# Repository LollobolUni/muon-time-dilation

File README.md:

# Cosmic muons and the stretching of time

A self-built experiment to measure the lifetime of cosmic-ray muons and to show, with data taken from cable cars in the Alps, that moving clocks run slow.

> [!TIP]
> New to the project? The [project overview (PDF)](docs/muon-time-dilation_project-overview.pdf) is a good place to start: in ten illustrated pages it explains the physics, how the detector works and what comes next.

Muons are created about 15 km above the ground and live on average 2.2 µs. Without special relativity almost none of them would reach the surface. The experiment has two parts:

1. **Muon lifetime at rest.** A one-litre plastic scintillator stops about a thousand muons a day. The time between the flash of the stopping muon and the flash of its decay electron gives the lifetime, with a target precision of 2–3%.
2. **Muon flux versus altitude.** Two small scintillator tiles in coincidence, with lead in between, count muons at 5–6 stops from Milan up to about 3000 m. Without time dilation the flux at 3000 m would be about 95 times that on the plain; with relativity, less than twice.

## Status

Design stage (November 2026). The electronics, firmware and mechanics are designed; the timer firmware has been tested on real hardware. Assembly and the first measurements are next.

## Repository structure

| Folder | Contents |
|---|---|
| `docs/` | Project overview (PDF) |
| `hardware/kicad/` | KiCad projects of the two circuit boards, with the project library |
| `hardware/schematics/` | Schematics and board layouts as PDF |
| `hardware/gerbers/` | Manufacturing files for the two boards |
| `hardware/bom/` | Bills of materials, one per board |
| `mechanics/parts/` | Parts to 3D-print, as STEP files |
| `mechanics/assemblies/` | Complete assemblies of the block detector and of the tile module |
| `mechanics/drawings/` | Drawings of the threaded inserts for the two enclosures |
| `firmware/timer/` | Four-channel timer for the Raspberry Pi Pico 2 |
| `firmware/pulse-generator/` | Test pulse generator for the timer (Raspberry Pi Pico 2) |
| `firmware/tools/` | Script to record a timer test from the PC |

## Hardware

| Board | Size | Function |
|---|---|---|
| PCB-401, channel board | 40 × 40 mm | One SiPM (onsemi MicroFC-60035) with bias filter, pulse shaping, amplifier (OPA356) and fast comparator (TLV3501). One board per SiPM; the same board fits the block and the tiles. |
| PCB-402, base board | 100 × 64 mm | Raspberry Pi Pico 2 W timer, SiPM bias supply (MAX5026, 22.1–28.2 V), analogue 3.3 V, four threshold outputs, four channel connectors, pressure sensor and microSD headers. |

- The KiCad projects are saved with KiCad 10. `PCB-402` uses the project library stored in the `PCB-401` folder, so keep the two folders side by side.
- Channel cables are straight six-way JST PH cables, pin 1 to pin 1: 1 HV, 2 GND, 3 THR, 4 +3.3 V analogue, 5 GND, 6 OUT.
- The SiPM centre paddle (pin 5) is left unsoldered.
- The bill of materials lists manufacturer and LCSC part numbers. Where the original part was not available, the substitute is noted in the `Note` column.

## Mechanics

The enclosures are designed for SLA printing in resin. Parts `3DP-301` (block enclosure) and `3DP-311` (tile enclosure, two copies) take four M3 × 6.25 mm threaded inserts each, as shown in the drawings. All parts are oriented with Z up and the opening towards +Z.

| Part | Quantity |
|---|---|
| `3DP-301` Block enclosure | 1 |
| `3DP-302` Block lid | 1 |
| `3DP-303` SiPM holder, block | 2 |
| `3DP-304` Spring caps (four joined) | 1 |
| `3DP-311` Tile enclosure | 2 |
| `3DP-312` Tile lid | 2 |
| `3DP-313` SiPM holder, tile | 2 |

## Firmware

The timer runs on a Raspberry Pi Pico 2 (the base board also accepts the Pico 2 W, which has the same pinout). It timestamps rising edges on GP2–GP5 with a step of two system-clock cycles (13.3 ns at 150 MHz), using one PIO state machine per channel and DMA. Events are sent over USB serial as `channel,time_in_steps`; lines starting with `#` are header and status lines.

Ready-to-flash `.uf2` files are included: hold BOOTSEL, connect the Pico and copy the file onto the drive that appears. To build from source with the Raspberry Pi Pico SDK (2.x):

```
cd firmware/timer
mkdir build && cd build
cmake .. -DPICO_SDK_PATH=/path/to/pico-sdk
make
```

The pulse generator produces pairs of pulses at known distances or with exponentially distributed delays (mean 2.197 µs), to test the timer before the detector is built. `firmware/tools/record_timer_test.py` records a test from both boards (requires `pyserial`).

## Author

Lorenzo Bologna, Physics Engineering, Politecnico di Milano.

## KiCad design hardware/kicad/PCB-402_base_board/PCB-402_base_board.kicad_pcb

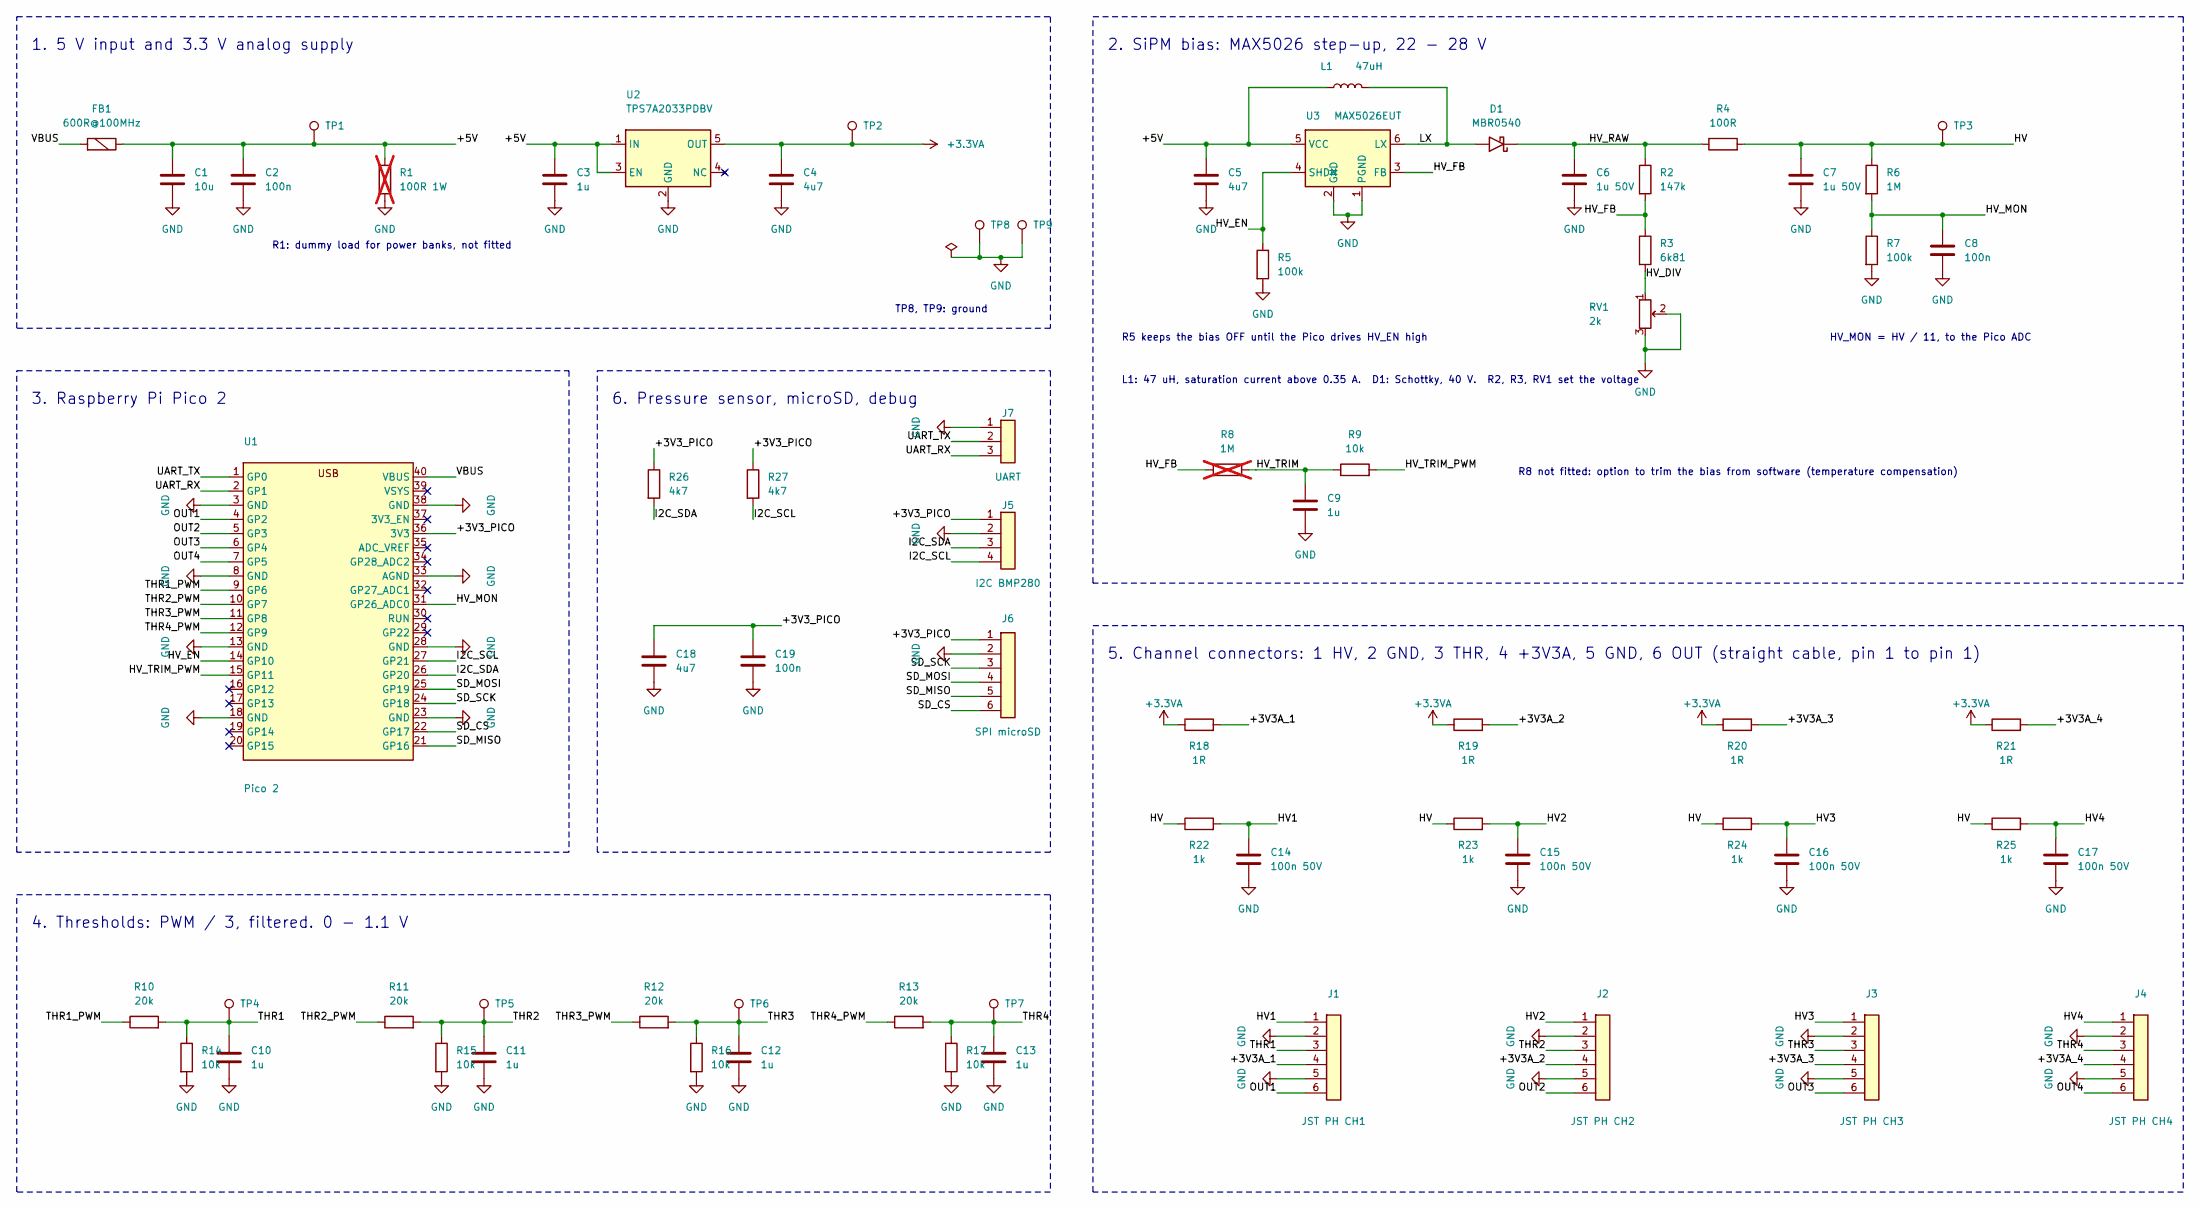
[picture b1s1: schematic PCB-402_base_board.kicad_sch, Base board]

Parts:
C1: 10u; C_0805_2012Metric_Pad1.18x1.45mm_HandSolder
C2, C8, C19: 100n; C_0805_2012Metric_Pad1.18x1.45mm_HandSolder
C3, C9, C10, C11, C12, C13: 1u; C_0805_2012Metric_Pad1.18x1.45mm_HandSolder
C4, C5, C18: 4u7; C_0805_2012Metric_Pad1.18x1.45mm_HandSolder
C6, C7: 1u 50V; C_0805_2012Metric_Pad1.18x1.45mm_HandSolder
C14, C15, C16, C17: 100n 50V; C_0805_2012Metric_Pad1.18x1.45mm_HandSolder
D1: MBR0540; D_SOD-123
FB1: 600R@100MHz; R_0805_2012Metric_Pad1.20x1.40mm_HandSolder
J1: JST PH CH1; JST_PH_B6B-PH-K_1x06_P2.00mm_Vertical
J2: JST PH CH2; JST_PH_B6B-PH-K_1x06_P2.00mm_Vertical
J3: JST PH CH3; JST_PH_B6B-PH-K_1x06_P2.00mm_Vertical
J4: JST PH CH4; JST_PH_B6B-PH-K_1x06_P2.00mm_Vertical
J5: I2C BMP280; PinHeader_1x04_P2.54mm_Vertical
J6: SPI microSD; PinHeader_1x06_P2.54mm_Vertical
J7: UART; PinHeader_1x03_P2.54mm_Vertical
L1: 47uH; L_Bourns_SRN6045TA
R1: 100R 1W; R_2512_6332Metric_Pad1.40x3.35mm_HandSolder; not fitted
R2: 147k; R_0805_2012Metric_Pad1.20x1.40mm_HandSolder
R3: 6k81; R_0805_2012Metric_Pad1.20x1.40mm_HandSolder
R4: 100R; R_0805_2012Metric_Pad1.20x1.40mm_HandSolder
R5, R7: 100k; R_0805_2012Metric_Pad1.20x1.40mm_HandSolder
R6: 1M; R_0805_2012Metric_Pad1.20x1.40mm_HandSolder
R8: 1M; R_0805_2012Metric_Pad1.20x1.40mm_HandSolder; not fitted
R9, R14, R15, R16, R17: 10k; R_0805_2012Metric_Pad1.20x1.40mm_HandSolder
R10, R11, R12, R13: 20k; R_0805_2012Metric_Pad1.20x1.40mm_HandSolder
R18, R19, R20, R21: 1R; R_0805_2012Metric_Pad1.20x1.40mm_HandSolder
R22, R23, R24, R25: 1k; R_1206_3216Metric_Pad1.30x1.75mm_HandSolder
R26, R27: 4k7; R_0805_2012Metric_Pad1.20x1.40mm_HandSolder
RV1: 2k; Potentiometer_Bourns_3296W_Vertical
TP1, TP2, TP3, TP4, TP5, TP6, TP7, TP8, TP9: TestPoint; TestPoint_Pad_D1.5mm
U1: Pico 2; RaspberryPi_Pico2_Sockets
U2: TPS7A2033PDBV; SOT-23-5
U3: MAX5026EUT; SOT-23-6

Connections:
+3.3VA: C4.1, R18.1, R19.1, R20.1, R21.1, TP2.1 (1_1), U2.5 (OUT)
/+3V3A_1: J1.4, R18.2
/+3V3A_2: J2.4, R19.2
/+3V3A_3: J3.4, R20.2
/+3V3A_4: J4.4, R21.2
/+3V3_PICO: C18.1, C19.1, J5.1, J6.1, R26.1, R27.1, U1.36 (3V3)
/+5V: C1.1, C2.1, C3.1, C5.1, FB1.2, L1.1, R1.1, TP1.1 (1_1), U2.1 (IN), U2.3 (EN), U3.5 (VCC)
/HV: C7.1, R4.2, R6.1, R22.1, R23.1, R24.1, R25.1, TP3.1 (1_1)
/HV1: C14.1, J1.1, R22.2
/HV2: C15.1, J2.1, R23.2
/HV3: C16.1, J3.1, R24.2
/HV4: C17.1, J4.1, R25.2
/HV_DIV: R3.2, RV1.1
/HV_EN: R5.1, U1.14 (GP10), U3.4 (SHDN)
/HV_FB: R2.2, R3.1, R8.1, U3.3 (FB)
/HV_MON: C8.1, R6.2, R7.1, U1.31 (GP26_ADC0)
/HV_RAW: C6.1, D1.1 (K), R2.1, R4.1
/HV_TRIM: C9.1, R8.2, R9.1
/HV_TRIM_PWM: R9.2, U1.15 (GP11)
/I2C_SCL: J5.4, R27.2, U1.27 (GP21)
/I2C_SDA: J5.3, R26.2, U1.26 (GP20)
/LX: D1.2 (A), L1.2, U3.6 (LX)
/OUT1: J1.6, U1.4 (GP2)
/OUT2: J2.6, U1.5 (GP3)
/OUT3: J3.6, U1.6 (GP4)
/OUT4: J4.6, U1.7 (GP5)
/SD_CS: J6.6, U1.22 (GP17)
/SD_MISO: J6.5, U1.21 (GP16)
/SD_MOSI: J6.4, U1.25 (GP19)
/SD_SCK: J6.3, U1.24 (GP18)
/THR1: C10.1, J1.3, R10.2, R14.1, TP4.1 (1_1)
/THR1_PWM: R10.1, U1.9 (GP6)
/THR2: C11.1, J2.3, R11.2, R15.1, TP5.1 (1_1)
/THR2_PWM: R11.1, U1.10 (GP7)
/THR3: C12.1, J3.3, R12.2, R16.1, TP6.1 (1_1)
/THR3_PWM: R12.1, U1.11 (GP8)
/THR4: C13.1, J4.3, R13.2, R17.1, TP7.1 (1_1)
/THR4_PWM: R13.1, U1.12 (GP9)
/UART_RX: J7.3, U1.2 (GP1)
/UART_TX: J7.2, U1.1 (GP0)
/VBUS: FB1.1, U1.40 (VBUS)
GND: C1.2, C2.2, C3.2, C4.2, C5.2, C6.2, C7.2, C8.2, C9.2, C10.2, C11.2, C12.2, C13.2, C14.2, C15.2, C16.2, C17.2, C18.2, C19.2, J1.2, J1.5, J2.2, J2.5, J3.2, J3.5, J4.2, J4.5, J5.2, J6.2, J7.1, R1.2, R5.2, R7.2, R14.2, R15.2, R16.2, R17.2, RV1.2, RV1.3, TP8.1 (1_1), TP9.1 (1_1), U1.3 (GND), U1.8 (GND), U1.13 (GND), U1.18 (GND), U1.23 (GND), U1.28 (GND), U1.33 (AGND), U1.38 (GND), U2.2 (GND), U3.1 (PGND), U3.2 (GND)

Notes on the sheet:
1. 5 V input and 3.3 V analog supply
R1: dummy load for power banks, not fitted
TP8, TP9: ground
2. SiPM bias: MAX5026 step-up, 22 - 28 V
R5 keeps the bias OFF until the Pico drives HV_EN high
L1: 47 uH, saturation current above 0.35 A. D1: Schottky, 40 V. R2, R3, RV1 set the voltage
HV_MON = HV / 11, to the Pico ADC
R8 not fitted: option to trim the bias from software (temperature compensation)
3. Raspberry Pi Pico 2
6. Pressure sensor, microSD, debug
4. Thresholds: PWM / 3, filtered. 0 - 1.1 V
5. Channel connectors: 1 HV, 2 GND, 3 THR, 4 +3V3A, 5 GND, 6 OUT (straight cable, pin 1 to pin 1)

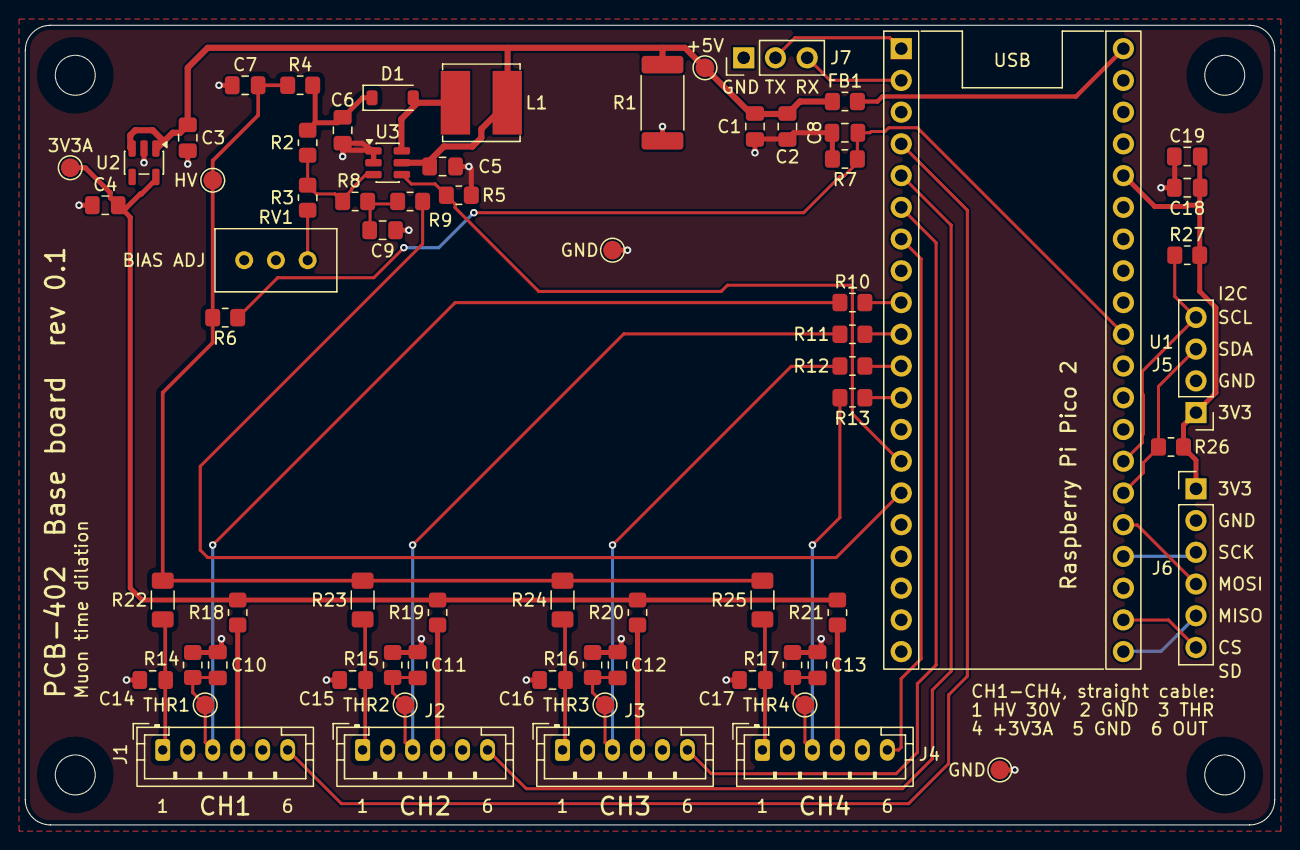
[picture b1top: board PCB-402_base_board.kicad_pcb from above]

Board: 2 copper layers, 100.0 x 64.0 mm, 73 parts (0 on the bottom side), 42 nets.

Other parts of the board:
H1, H2, H3, H4: M3; MountingHole_3.2mm_M3

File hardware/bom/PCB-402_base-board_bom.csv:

References,Qty,Value,Footprint,Manufacturer,MPN,LCSC,Note,Description
C1,1,10u,C_0805_2012Metric_Pad1.18x1.45mm_HandSolder,TDK,C2012X5R1E106KT000N,C329933,,Unpolarized capacitor
"C2, C8, C19",3,100n,C_0805_2012Metric_Pad1.18x1.45mm_HandSolder,Samsung,CL21B104KBCNNNC,C1711,,Unpolarized capacitor
"C3, C9, C10, C11, C12, C13",6,1u,C_0805_2012Metric_Pad1.18x1.45mm_HandSolder,YAGEO,CC0805KKX7R9BB105,C91185,,Unpolarized capacitor
"C4, C5, C18",3,4u7,C_0805_2012Metric_Pad1.18x1.45mm_HandSolder,Samsung,CL21A475KAQNNNE,C1779,,Unpolarized capacitor
"C6, C7",2,1u 50V,C_0805_2012Metric_Pad1.18x1.45mm_HandSolder,YAGEO,CC0805KKX7R9BB105,C91185,,Unpolarized capacitor
"C14, C15, C16, C17",4,100n 50V,C_0805_2012Metric_Pad1.18x1.45mm_HandSolder,Samsung,CL21B104KBCNNNC,C1711,,Unpolarized capacitor
D1,1,MBR0540,D_SOD-123,onsemi,MBR0540T1G,C21353,,"Schottky diode, pin 1 = cathode"
FB1,1,600R@100MHz,R_0805_2012Metric_Pad1.20x1.40mm_HandSolder,Murata,BLM21PG331SN1D,C74764,BLM21PG331 (330 R at 100 MHz) used: the 600 R BLM21PG601SN1D is the original choice,Ferrite bead
J1,1,JST PH CH1,JST_PH_B6B-PH-K_1x06_P2.00mm_Vertical,JST,B6B-PH-K-S(LF)(SN),C131342,,"Generic connector, single row, 01x06"
J2,1,JST PH CH2,JST_PH_B6B-PH-K_1x06_P2.00mm_Vertical,JST,B6B-PH-K-S(LF)(SN),C131342,,"Generic connector, single row, 01x06"
J3,1,JST PH CH3,JST_PH_B6B-PH-K_1x06_P2.00mm_Vertical,JST,B6B-PH-K-S(LF)(SN),C131342,,"Generic connector, single row, 01x06"
J4,1,JST PH CH4,JST_PH_B6B-PH-K_1x06_P2.00mm_Vertical,JST,B6B-PH-K-S(LF)(SN),C131342,,"Generic connector, single row, 01x06"
J5,1,I2C BMP280,PinHeader_1x04_P2.54mm_Vertical,BOOMELE,2.54-1*40P,C2337,cut from one 1x40 header strip,"Generic connector, single row, 01x04"
J6,1,SPI microSD,PinHeader_1x06_P2.54mm_Vertical,BOOMELE,2.54-1*40P,C2337,cut from one 1x40 header strip,"Generic connector, single row, 01x06"
J7,1,UART,PinHeader_1x03_P2.54mm_Vertical,BOOMELE,2.54-1*40P,C2337,cut from one 1x40 header strip,"Generic connector, single row, 01x03"
L1,1,47uH,L_Bourns_SRN6045TA,SXN,SMNR6045-470MT,C135307,"alternative to Bourns SRN6045TA-470M, same footprint",Inductor
R1,1,100R 1W,R_2512_6332Metric_Pad1.40x3.35mm_HandSolder,,,,"not fitted; dummy load for power banks, optional",Resistor
R2,1,147k,R_0805_2012Metric_Pad1.20x1.40mm_HandSolder,YAGEO,RC0805FR-07147KL,C483012,,Resistor
R3,1,6k81,R_0805_2012Metric_Pad1.20x1.40mm_HandSolder,YAGEO,AC0805FR-076K81L,C228970,,Resistor
R4,1,100R,R_0805_2012Metric_Pad1.20x1.40mm_HandSolder,YAGEO,RC0805FR-07100RL,C105577,,Resistor
"R5, R7",2,100k,R_0805_2012Metric_Pad1.20x1.40mm_HandSolder,YAGEO,RC0805FR-07100KL,C96346,,Resistor
R6,1,1M,R_0805_2012Metric_Pad1.20x1.40mm_HandSolder,YAGEO,RC0805FR-071ML,C107700,,Resistor
R8,1,1M,R_0805_2012Metric_Pad1.20x1.40mm_HandSolder,,,,not fitted; option for software bias trim,Resistor
"R9, R14, R15, R16, R17",5,10k,R_0805_2012Metric_Pad1.20x1.40mm_HandSolder,YAGEO,RC0805FR-0710KL,C84376,,Resistor
"R10, R11, R12, R13",4,20k,R_0805_2012Metric_Pad1.20x1.40mm_HandSolder,YAGEO,RC0805FR-0720KL,C114566,,Resistor
"R18, R19, R20, R21",4,1R,R_0805_2012Metric_Pad1.20x1.40mm_HandSolder,YAGEO,RC0805FR-071RL,C131397,,Resistor
"R22, R23, R24, R25",4,1k,R_1206_3216Metric_Pad1.30x1.75mm_HandSolder,YAGEO,RC1206FR-071KL,C131398,,Resistor
"R26, R27",2,4k7,R_0805_2012Metric_Pad1.20x1.40mm_HandSolder,YAGEO,RC0805FR-074K7L,C60816,,Resistor
RV1,1,2k,Potentiometer_Bourns_3296W_Vertical,Bourns,3296W-1-202LF,C83684,,"Trimmer potentiometer, pin 2 = wiper"
U1,1,Pico 2,RaspberryPi_Pico2_Sockets,Kinghelm,KH-2.54FH-1X20P-H8.5,C2905423,two 1x20 sockets (order qty 2); module: Raspberry Pi Pico 2 W,"Raspberry Pi Pico 2 on two 1x20 sockets, top view, USB at the top"
U2,1,TPS7A2033PDBV,SOT-23-5,Texas Instruments,TLV75533PDBVR,C404027,TLV75533P fitted in place of the TPS7A2033 (unavailable),"Texas Instruments TPS7A20 low-noise 300 mA LDO, fixed output, SOT-23-5"
U3,1,MAX5026EUT,SOT-23-6,Analog Devices,MAX5026EUT+T,C87603,,"Analog Devices MAX5026, 500 kHz step-up converter, adjustable up to 36 V, SOT-23-6"

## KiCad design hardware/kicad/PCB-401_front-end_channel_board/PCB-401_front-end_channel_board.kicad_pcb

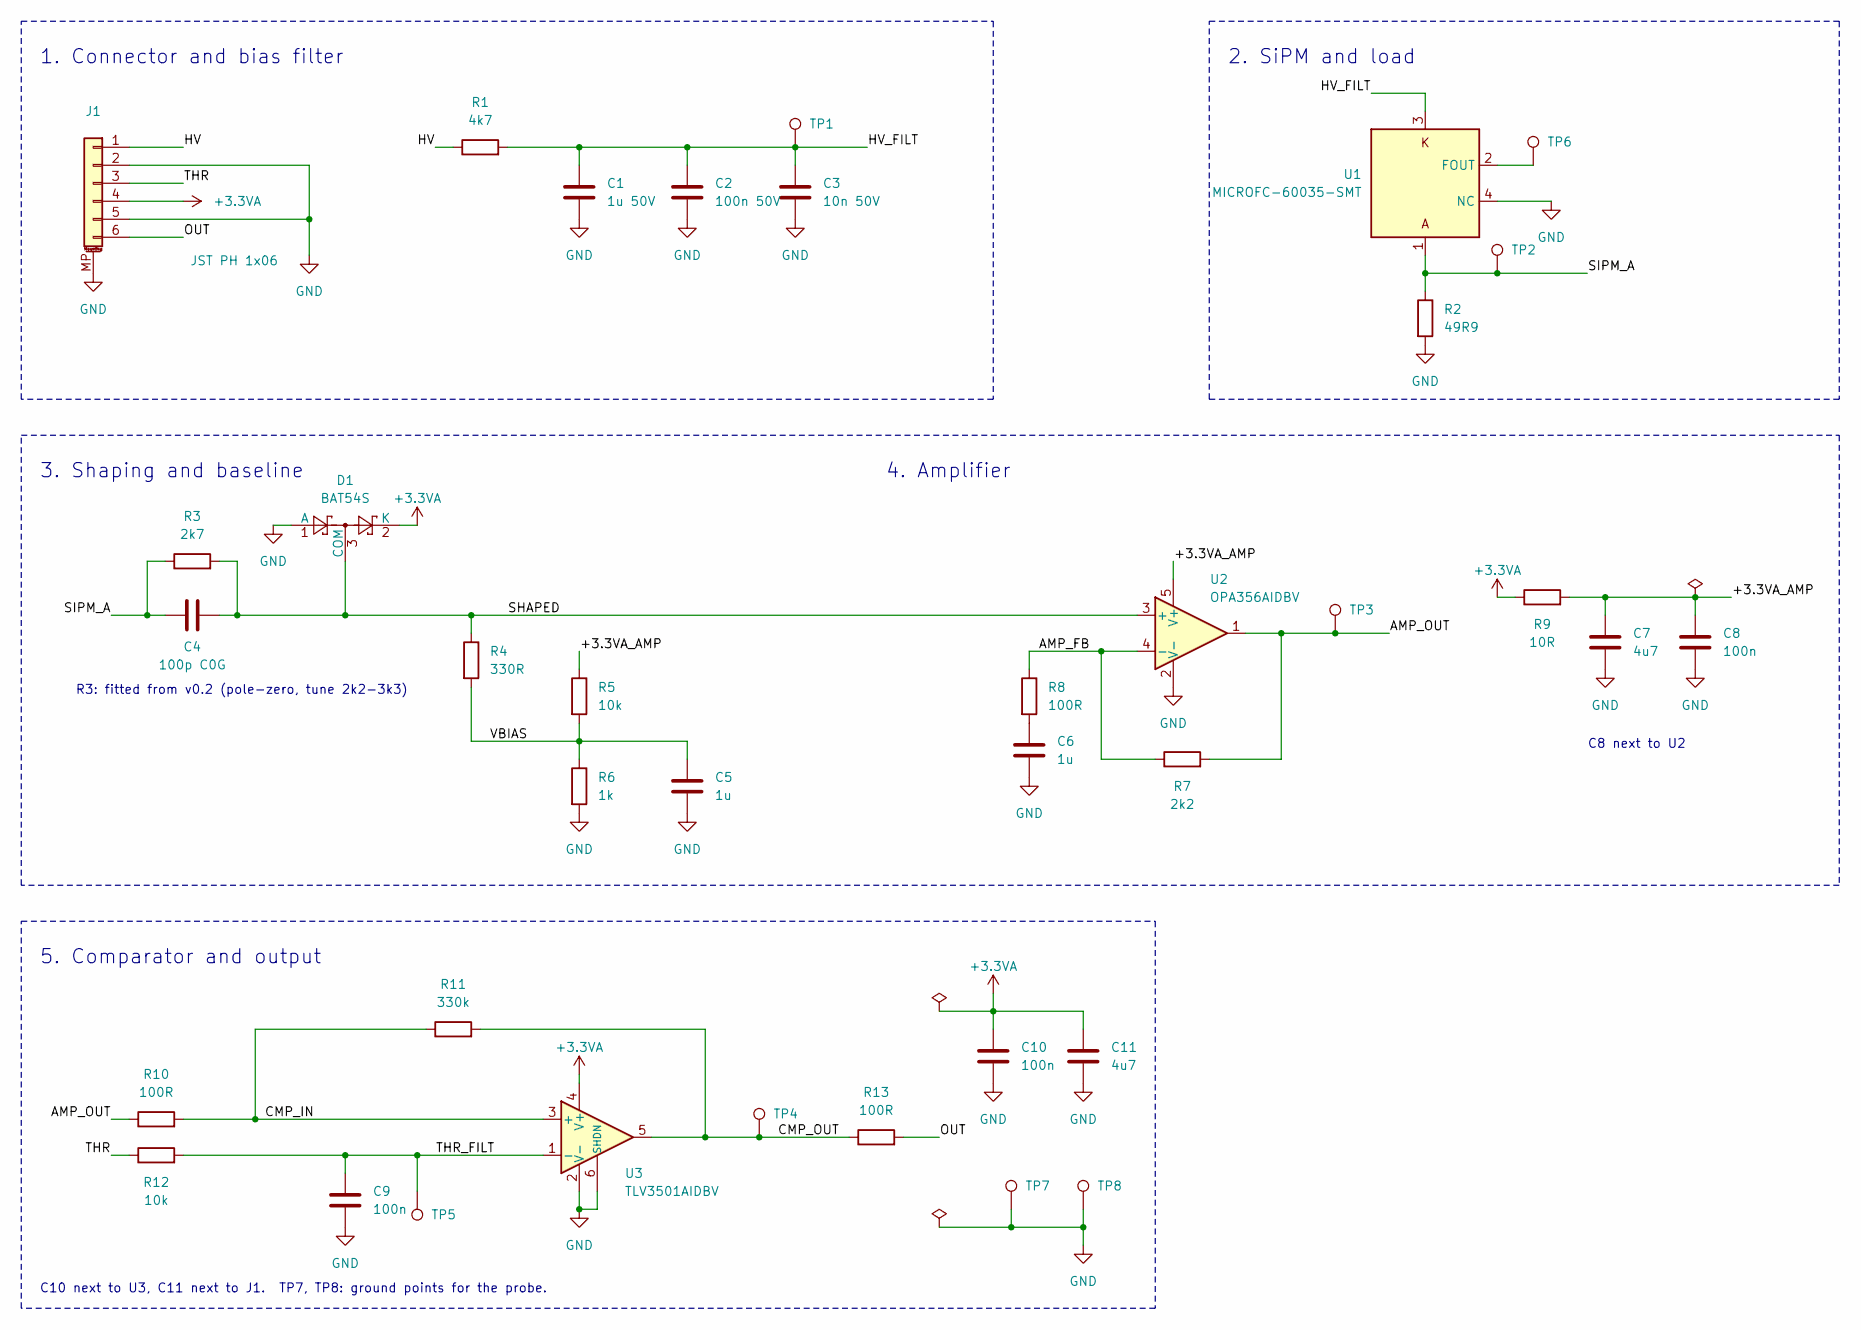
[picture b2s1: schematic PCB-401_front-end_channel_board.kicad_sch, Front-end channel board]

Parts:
C1: 1u 50V; C_0805_2012Metric_Pad1.18x1.45mm_HandSolder
C2: 100n 50V; C_0805_2012Metric_Pad1.18x1.45mm_HandSolder
C3: 10n 50V; C_0805_2012Metric_Pad1.18x1.45mm_HandSolder
C4: 100p C0G; C_0805_2012Metric_Pad1.18x1.45mm_HandSolder
C5, C6: 1u; C_0805_2012Metric_Pad1.18x1.45mm_HandSolder
C7, C11: 4u7; C_0805_2012Metric_Pad1.18x1.45mm_HandSolder
C8, C9, C10: 100n; C_0805_2012Metric_Pad1.18x1.45mm_HandSolder
D1: BAT54S; SOT-23
J1: JST PH 1x06; JST_PH_S6B-PH-SM4-TB_1x06-1MP_P2.00mm_Horizontal
R1: 4k7; R_0805_2012Metric_Pad1.20x1.40mm_HandSolder
R2: 49R9; R_0805_2012Metric_Pad1.20x1.40mm_HandSolder
R3: 2k7; R_0805_2012Metric_Pad1.20x1.40mm_HandSolder
R4: 330R; R_0805_2012Metric_Pad1.20x1.40mm_HandSolder
R5, R12: 10k; R_0805_2012Metric_Pad1.20x1.40mm_HandSolder
R6: 1k; R_0805_2012Metric_Pad1.20x1.40mm_HandSolder
R7: 2k2; R_0805_2012Metric_Pad1.20x1.40mm_HandSolder
R8, R10, R13: 100R; R_0805_2012Metric_Pad1.20x1.40mm_HandSolder
R9: 10R; R_0805_2012Metric_Pad1.20x1.40mm_HandSolder
R11: 330k; R_0805_2012Metric_Pad1.20x1.40mm_HandSolder
TP1, TP2, TP3, TP4, TP5, TP6, TP7, TP8: TestPoint; TestPoint_Pad_D1.5mm
U1: MICROFC-60035-SMT
U2: OPA356AIDBV; SOT-23-5
U3: TLV3501AIDBV; SOT-23-6

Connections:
+3.3VA: C10.1, C11.1, D1.2 (K), J1.4, R9.1, U3.4 (V+)
/+3.3VA_AMP: C7.1, C8.1, R5.1, R9.2, U2.5 (V+)
/AMP_FB: R7.1, R8.1, U2.4 (-)
/AMP_OUT: R7.2, R10.1, TP3.1 (1_1), U2.1
/CMP_IN: R10.2, R11.1, U3.3 (+)
/CMP_OUT: R11.2, R13.1, TP4.1 (1_1), U3.5
/HV: J1.1, R1.1
/HV_FILT: C1.1, C2.1, C3.1, R1.2, TP1.1 (1_1), U1.3
/OUT: J1.6, R13.2
/SHAPED: C4.2, D1.3 (COM), R3.2, R4.1, U2.3 (+)
/SIPM_A: C4.1, R2.1, R3.1, TP2.1 (1_1), U1.1
/THR: J1.3, R12.1
/THR_FILT: C9.1, R12.2, TP5.1 (1_1), U3.1 (-)
/VBIAS: C5.1, R4.2, R5.2, R6.1
GND: C1.2, C2.2, C3.2, C5.2, C6.2, C7.2, C8.2, C9.2, C10.2, C11.2, D1.1 (A), J1.2, J1.5, J1.MP (MountPin), R2.2, R6.2, TP7.1 (1_1), TP8.1 (1_1), U1.4 (NC), U2.2 (V-), U3.2 (V-), U3.6 (SHDN)
unnamed: C6.1, R8.2
unnamed: TP6.1 (1_1), U1.2 (FOUT)

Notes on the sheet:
2. SiPM and load
C8 next to U2
4. Amplifier
3. Shaping and baseline
5. Comparator and output
C10 next to U3, C11 next to J1. TP7, TP8: ground points for the probe.
1. Connector and bias filter
R3: fitted from v0.2 (pole-zero, tune 2k2-3k3)

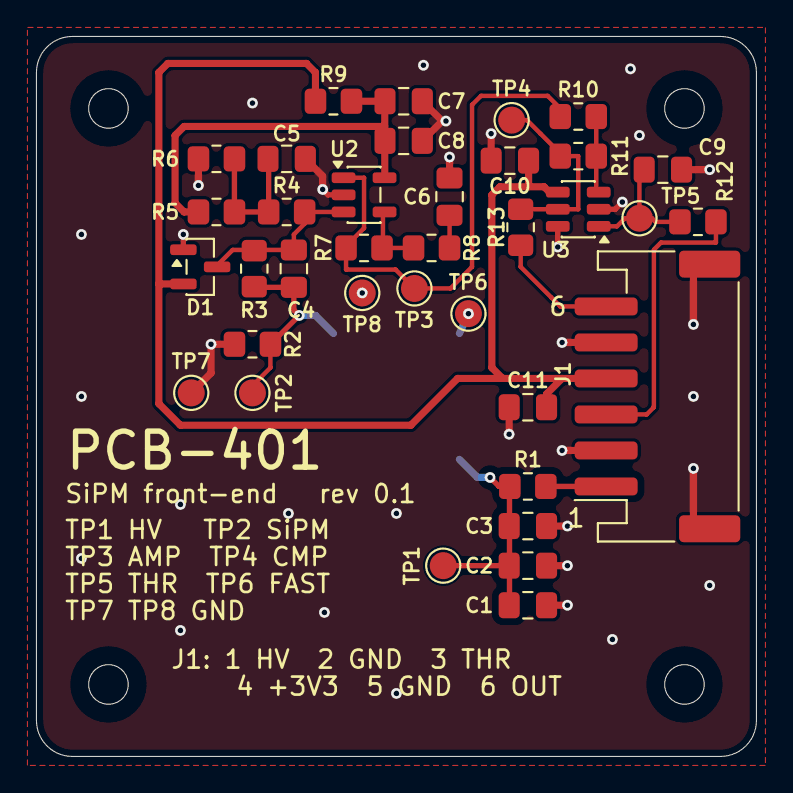
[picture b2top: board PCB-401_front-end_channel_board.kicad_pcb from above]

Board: 2 copper layers, 40.0 x 40.0 mm, 41 parts (1 on the bottom side), 17 nets.

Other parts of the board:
H1, H2, H3, H4: MountingHole_2.2mm_NPTH

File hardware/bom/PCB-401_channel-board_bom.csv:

References,Qty,Value,Footprint,Manufacturer,MPN,LCSC,Note,Description
C1,1,1u 50V,C_0805_2012Metric_Pad1.18x1.45mm_HandSolder,YAGEO,CC0805KKX7R9BB105,C91185,,Unpolarized capacitor
C2,1,100n 50V,C_0805_2012Metric_Pad1.18x1.45mm_HandSolder,Samsung,CL21B104KBCNNNC,C1711,,Unpolarized capacitor
C3,1,10n 50V,C_0805_2012Metric_Pad1.18x1.45mm_HandSolder,YAGEO,CC0805KRX7R9BB103,C83170,,Unpolarized capacitor
C4,1,100p C0G,C_0805_2012Metric_Pad1.18x1.45mm_HandSolder,Samsung,CL21C101JBANNNC,C1790,"starting value, tune at bring-up",Unpolarized capacitor
"C5, C6",2,1u,C_0805_2012Metric_Pad1.18x1.45mm_HandSolder,YAGEO,CC0805KKX7R9BB105,C91185,,Unpolarized capacitor
"C7, C11",2,4u7,C_0805_2012Metric_Pad1.18x1.45mm_HandSolder,Samsung,CL21A475KAQNNNE,C1779,,Unpolarized capacitor
"C8, C9, C10",3,100n,C_0805_2012Metric_Pad1.18x1.45mm_HandSolder,Samsung,CL21B104KBCNNNC,C1711,,Unpolarized capacitor
D1,1,BAT54S,SOT-23,Nexperia,"BAT54S,215",C47546,,"Vr 30V, If 200mA, Dual schottky barrier diode, in series, SOT-323"
J1,1,JST PH 1x06,JST_PH_S6B-PH-SM4-TB_1x06-1MP_P2.00mm_Horizontal,JST,S6B-PH-SM4-TB(LF)(SN),C265405,,"Generic connectable mounting pin connector, single row, 01x06, script generated (kicad-library-utils/schlib/autogen/connector/)"
R1,1,4k7,R_0805_2012Metric_Pad1.20x1.40mm_HandSolder,YAGEO,RC0805FR-074K7L,C60816,,Resistor
R2,1,49R9,R_0805_2012Metric_Pad1.20x1.40mm_HandSolder,YAGEO,RC0805FR-0749R9L,C132320,"starting value, tune at bring-up",Resistor
R3,1,2k7,R_0805_2012Metric_Pad1.20x1.40mm_HandSolder,YAGEO,RC0805FR-072K7L,C114520,"pole-zero, tune 2k2-3k3 at bring-up",Resistor
R4,1,330R,R_0805_2012Metric_Pad1.20x1.40mm_HandSolder,YAGEO,RC0805FR-07330RL,C105878,,Resistor
"R5, R12",2,10k,R_0805_2012Metric_Pad1.20x1.40mm_HandSolder,YAGEO,RC0805FR-0710KL,C84376,,Resistor
R6,1,1k,R_0805_2012Metric_Pad1.20x1.40mm_HandSolder,YAGEO,RC0805FR-071KL,C95781,,Resistor
R7,1,2k2,R_0805_2012Metric_Pad1.20x1.40mm_HandSolder,YAGEO,RC0805FR-072K2L,C114561,,Resistor
"R8, R10, R13",3,100R,R_0805_2012Metric_Pad1.20x1.40mm_HandSolder,YAGEO,RC0805FR-07100RL,C105577,,Resistor
R9,1,10R,R_0805_2012Metric_Pad1.20x1.40mm_HandSolder,YAGEO,RC0805FR-0710RL,C96347,,Resistor
R11,1,330k,R_0805_2012Metric_Pad1.20x1.40mm_HandSolder,YAGEO,RC0805FR-07330KL,C114528,,Resistor
U1,1,MICROFC-60035-SMT,MICROFC-60035-SMT,onsemi,MICROFC-60035-SMT-TR,,"SiPM, Mouser 863-MFC60035SMTTR (not the TR1 variant)","onsemi C-Series SiPM, 6 mm, 35 um microcells, SMT. Pin 5 (paddle) not soldered"
U2,1,OPA356AIDBV,SOT-23-5,Texas Instruments,OPA356AIDBVR,C183100,,"Single High Speed CMOS Operational Amplifier, SOT-23-5"
U3,1,TLV3501AIDBV,SOT-23-6,Texas Instruments,TLV3501AIDBVR,C193413,,"High-Speed Comparator, 4.5-ns, Rail-to-Rail, Push-Pull CMOS Output, SOT-23-6"
